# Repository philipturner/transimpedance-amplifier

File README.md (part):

# Transimpedance Amplifier

<p align="center">
&nbsp;
  
&nbsp;&nbsp;
  
&nbsp;&nbsp;
  
&nbsp;
</p>

Phase 0.1 of the [APM Roadmap](https://github.com/philipturner/apm-roadmap)

Objective: Gather as much data as possible about the TIA sensor of an STM, using both theory and experiment.

Deadline: September 30, 2025 for the first physical prototype

Completed: November 7, 2025

Table of Contents:
- [July 26, 2025](#july-26-2025)
- [July 27, 2025](#july-27-2025)
- [July 28, 2025](#july-28-2025)
- [July 29, 2025](#july-29-2025)
- [August 3, 2025](#august-3-2025)
- [August 4, 2025](#august-4-2025)
- [August 5, 2025](#august-5-2025)
- [August 6, 2025](#august-6-2025)
- [August 7, 2025](#august-7-2025)
- [August 8, 2025](#august-8-2025)
- [August 9, 2025](#august-9-2025)
- [August 16, 2025](#august-16-2025)
- [August 18, 2025](#august-18-2025)
- [August 20, 2025](#august-20-2025)
- [August 22, 2025](#august-22-2025)
- [August 23, 2025](#august-23-2025)
- [August 26, 2025](#august-26-2025)
- [August 27, 2025](#august-27-2025)
- [August 28, 2025](#august-28-2025)
- [August 29, 2025](#august-29-2025)
- [September 1, 2025](#september-1-2025)
- [September 7, 2025](#september-7-2025)
- [September 8, 2025](#september-8-2025)
- [September 9, 2025](#september-9-2025)
- [September 10, 2025](#september-10-2025)
- [September 11, 2025](#september-11-2025)
- [September 12, 2025](#september-12-2025)
- [September 15, 2025](#september-15-2025)
- [September 16, 2025](#september-16-2025)
- [September 17, 2025](#september-17-2025)
- [September 18, 2025](#september-18-2025)
- [September 19, 2025](#september-19-2025)
- [September 20, 2025](#september-20-2025)
- [September 21, 2025](#september-21-2025)
- [September 22, 2025](#september-22-2025)
- [September 23, 2025](#september-23-2025)
- [September 24, 2025](#september-24-2025)
- [September 25, 2025](#september-25-2025)
- [October 22, 2025](#october-22-2025)
- [October 23, 2025](#october-23-2025)
- [October 24, 2025](#october-24-2025)
- [October 26, 2025](#october-26-2025)
- [October 29, 2025](#october-29-2025)
- [October 30, 2025](#october-30-2025)
- [October 31, 2025](#october-31-2025)
- [November 2, 2025](#november-2-2025)
- [November 3, 2025](#november-3-2025)
- [November 5, 2025](#november-5-2025)
- [November 6, 2025](#november-6-2025)
- [November 7, 2025](#november-7-2025)

## July 26, 2025

Three simulation tasks, in chronological order
1) Understand/simulate why coarse tip approach takes so long
    - Understand specific algorithms for moving the coarse motor (approach & retract) without frictional backlash causing a tip crash
    - Understand maximum speeds of piezo motors
2) Simulate imperfect DAC-driven cancellation with a fixed value compensation capacitor
    - Use the tip-sample capacitance of a plausible geometry, derived with FEA
    - Include a finite insulation resistance
3) Fully understand the art of cabling analog lines in/out of UHV chambers + instrumentation amplifiers + ground loops
    - Include EMI and digital coupling from the bias DAC + ADC + SPI ports + power supply system

Notes about simulations:
- Make compromises to reduce the number of variables in each simulation, making it practical to set up
    - The simulations are not particularly computationally intensive, often 1-variable analytical functions, Fourier transforms, and integrals of power spectral density.
    - Likely using a combination of Google Sheets and single-file scripts hosted on GitHub Gist, hyperlinked to this repo.
- Exploit recently acquired skills in finite element analysis and the theory of EMI/grounding/shielding
- <b>Early IRL hardware tests may fail some requirements for system performance</b>, which are assumed or optimized for in the simulations

---

Simultaneously performing a low-cost physical test with a badly shielded IRL model
- Gather as much data, as early as possible
- Pipeline the phases of design elaboration
- Later stages include electromagnetic shielding, interfaces with automated electronics for the I/O voltages, then the logical transition to Phase 0.2

Primary blockers to first physical prototype:
- Lack of understanding about electrical performance of reversible DUT connection point (DUT = resistor, capacitor)
- Need to elaborate on requirements for ventilation from acid fumes, and other specific equipment to order for hand soldering
- Need to resolve the issues with incorrect/unnecessary bypass/decoupling capacitors
  - It is a very bad idea to omit all the capacitors, without at least giving it some rigorous consideration
- Need to resolve the missing/incorrect KiCad symbols and footprints for each IC. Organize the footprints on a physical PCB model and become familiar with the specific pin functions & positions.
- Need to clarify the bothersome trace width variable

<b>Fast-track work on the physical prototype.</b> Ensure that all fabrication equipment, testing equipment, and circuit parts are delivered by August 12, 2025. In any leftover time until August 12, I can return to the three simulation tasks.

An appropriate name for this is ["STM Experiment #3"](https://www.youtube.com/watch?v=IUPDecnuzO4). The experiments may not logically build on each other. For example, a single 1000 V linear amplifier doesn't logically follow a capacitive displacement sensor. However, it can still be catalogued as `n + 1` to show the iterative nature of design elaboration & exploration.

## July 27, 2025

One of the most important tests should be feedback loop stability. With the SPICE simulations, I can predict what values for input capacitance will send the circuit into oscillations. Pick a conservative value(s) for a capacitor DUT that satisfies this condition, without making the current exceed its dynamic range (simply reduce the frequency of the signal).

The first prototype will test two TIA variants. The first will be the standard OPA627 + 100 MΩ design used in most DIY STM projects. This will give a baseline for tracing failures, if the complex 2-stage design does not work at all.

I should see whether testing equipment, such as a handheld oscilloscope, can generate an input function. This would remove the need for a hard-coded triangle wave generator on the PCB. However, I might include the triangle wave generator anyway, for completeness and/or more debugging options. It also provides experience designing with digital/nonlinear components (comparator & Schmitt trigger), which may couple into the analog components against my wishes. There should be a simple way to disconnect the generator from power pins. It could be helpful to make the generator's capacitor swappable, so the frequency can change.

## July 28, 2025

I am starting to read large swaths of the IPC 7351 standard, February 2005 revision. This project will resolve my frustration with non-standardization of resistor & capacitor footprints. It substantiates a growing realization across many engineering projects, that complex systems have many variables. They demand significant amounts of data to wrap my head around. I am not satisfied with arbitrary guesses and binary yes/no "it worked" tests, with no explanation of how this choice contributed to a reduction in UHV chamber cost.

> My objective is obtain better control over the usability, performance, and cost of my end product(s).

I feel more comfortable creating my own footprints from scratch, where I can trust every parameter used to derive every dimension. I will compare my footprints to those from vendors, SnapEDA, and KiCad libraries.

## July 29, 2025

A few more things I want to do, before the 1st prototype:
- Run a SPICE simulation of the stability of a feedback loop with OPA627 + 100 MΩ. Check the limits of stability with the parasitic capacitance of the resistor.
  - Include a model of OPA637 to understand why that's not okay.
  - If OPA637 passes in the simulations, the test board will include a third TIA, OPA637 + 100 MΩ + no parallel capacitor.
    - Even if it doesn't pass, include the actual combination IRL, to prove that it oscillates when tested!
    - Unless this could plausibly impair the operation of the other amplifiers, and there's no way to switch off power to the OPA637.
    - Will severe oscillation conditions cause damage to the component and/or its power supply?
- Get more rigorous calculations of the parasitics for the components, and of the potentiometers.
- Design custom footprints for the capacitors and trimpots as well, in the first step. I previously planned to just wrap my head around the ICs + large resistors first. Instead, I should get the entire system specified at the highest (symbolic) level, and elaborate on the physical layout once that's fixed.
  - Bypass/decoupling capacitors are intentionally omitted at this stage.
  - The exact resistor values for the AD8615 voltage divider are omitted at this stage. Also not worrying about whether the two polarities of the divider cross through the GND net.
- Calculate the expected noise (e.g. Johnson noise from resistors in 2nd stage), bandwidth of the oscilloscope ADC, and consider electromagnetic shielding.
  - Consider an artificial bandwidth limiter with a transfer function similar to the ADS8699. This probably requires another IC. Good practice in selecting arbitrary op-amps for real world situations of need.
  - Calculate the leakage current at the physical current input junction + corresponding reversible DUT port. Compare the leakage current to the noise floor.
- Prepare a list of through-hole DUT components. Elaborate on whether it's a single DUT port for all 2&ndash;3 amplifiers, or a separate port for each.

I just learned/remembered that OPA627 and OPA637 are very old and expensive (\~$30). I'll have to revise these plans, to use newer and cheaper chips like OPA828 (\~$7). Or scrap the entire concept of additional 1-stage amplifiers to save time, depending on motivation.

## August 3, 2025

This project is on track to blow far north of its time budget. I'll have to compromise.

Permitted:
- Delete the oscilloscope from the workflow (yay!)
- Read [MT-015](https://www.analog.com/media/en/training-seminars/tutorials/MT-015.pdf), [MT-017](https://www.analog.com/media/en/training-seminars/tutorials/MT-017.pdf), [MT-019](https://www.analog.com/media/en/training-seminars/tutorials/MT-019.pdf), [MT-021](https://www.analog.com/media/en/training-seminars/tutorials/MT-021.pdf), [MT-090](https://www.analog.com/media/en/training-seminars/tutorials/MT-090.pdf) to understand the chips I'm working with
- Make an entirely custom footprint for every electronic part

Disallowed:
- Run a simulation to understand whether quantization noise and time jitter makes capacitance compensation unviable, with my novel approach
- Use any chips that require reflow soldering
- The analog triangle wave generator from the fast low-noise TIA paper. We're already synthesizing arbitrary waveforms with the DAC, with adjustable frequencies.

The near-term deliverable will pair the Teensy with a single DAC channel (DAC81401) and a single ADC channel (ADS8699), with a nerfed system bandwidth of 15 kHz. I really wanted a higher frequency to debug the first step. Unfortunately, the 500 kHz chip, ADS86861W, requires reflow soldering. I'll defer contemplating the ramifications of this omission to a later date.

---

Comments on the previous journal entry:
- Johnson noise is comparable to e<sub>n</sub>C noise, at 15 kHz bandwidth + 2nd order rolloff.
  - 6σ noise from capacitance is <b>5.2 pA</b>, provided just the 9.2 pF input capacitance of the AD8615 (conservative estimate, summing the differential and common-mode capacitance)
  - 6σ noise from capacitance is <b>24.7 pA</b>, when moved outside the UHV chamber, adding 35 pF to the capacitance to model a coaxial cable
  - 6σ Johnson noise from a 100 MΩ resistor is <b>10.9 pA</b>
  - 6σ Johnson noise from a 300 MΩ resistor is <b>6.3 pA</b>
  - 6σ Johnson noise from a 1 GΩ resistor is <b>3.5 pA</b>
- The noise signal appears as ~1 mV at the ADC.
  - 1-stage with OPA828ID:
    - 15.0 pF
    - 100 MΩ
    - 6σ noise envelope is <b>1.2 mV</b>
  - 2-stage with AD8615:
    - 9.2 pF
    - 300 MΩ
    - 6σ noise envelope is <b>2.4 mV</b>
- Don't need to construct an artificial 15 kHz filter out of discrete components. I'm using the actual ADS8699 chip in the circuit board now.
- 15 kHz bandwidth is more than enough for the STM feedback loop. If anything, I would use digital filtering to reduce it to the single kHz range, reducing the 6σ current noise to ~1 pA.

Source: [Transimpedance Amplifier (Google Sheets)](https://docs.google.com/spreadsheets/d/1QVJOiaRJbdRXN7CXii3z91K5A64h3VmgLCsRjpDpIrQ/edit?usp=sharing)

## August 4, 2025

<p align="center">
&nbsp;
  
&nbsp;&nbsp;
  
&nbsp;
</p>

## August 5, 2025

It is becoming very clear that I want to run this simulation about capacitive displacement sensing.

The simulation will have an analytical (frequency domain) and numerical (time domain) part.
- Analytical stuff:
  - Theoretical model of the distribution of quantization noise among the DACs (evenly across the Nyquist bandwidth)
    - Ensure the sine wave frequency is indivisible by the quantization frequency (100 kSPS)
    - Concerned about the variable-voltage approach not being able to perfectly cancel the quantization noise
  - Model of the integrated e<sub>n</sub>C noise after lock-in amplification
  - Model of the transfer function for the 2-stage TIA, which might change with input capacitance (?)
- Numerical stuff:
  - FP64 for the simulations to avoid concerns about rounding error, over long time intervals for lock-in amplification
    - Time stepping resolution 1&ndash;2 orders of magnitude better than the 100 kSPS sampling rate
  - Exact algorithm for a digital filter approximating a first-order or second-order lowpass
    - Validate that the filters have the expected gain falloff, by running a sweep over sine wave frequencies
    - The filter is affected by the time step size
  - Simulate the two DACs being out of sync, which probably cannot be represented in an analytical frequency domain model
- A way to include the effects of shot noise from background capacitance into the results of the numerical part

Imperfections covered in the simulation:
- Inaccurate matching of a fixed-value capacitor to the tip-sample capacitance (up to a factor of 10 in either direction)
- Overloading the maximum TIA voltage due to the transfer function exceeding the ADC @ 15 kHz. Specifically, overloading from signals in the 15&ndash;30 kHz range.
- Quantization of the two DAC signals causing a strange division of the Gaussian quantization errors (?)
- The two DACs being out of sync (not yet figured out the exact amount of delay to test)

Imperfections not covered:
- Time jitter in the ADC and/or DACs
- Switching transients in the DACs
- Interference from acoustic noise
- Interference from a finite insulation resistance in the compensation capacitor

First step:
- Attempt to find a formula for the RMS current of two cancelling signals, slightly phase shifted
- Address the low-hanging fruit, of a frequency domain analysis of the effect of quantization noise

Second step:
- Refresh myself on the analytical formulas for transfer function of the fast low-noise TIA, stability conditions, and location of the 2nd pole
- Figure out the exact potentiometer values appropriate for this circuit
- For simplicity (to save time), the simulation will assume the potentiometers are perfectly matched, to an infinite resolution

Since I am in the car right now, I cannot work on the first step. Therefore, I will proceed with specifying the near-term experiment with reduced scope.

---

Interesting observations:
- ADS8681W is not even in stock, although Mouser expects a new batch in late August
- Only Mouser has stock of DAC81402, DigiKey does not
- Amazon Basics 6LR61 is probably sufficient for the 9V batteries

## August 6, 2025

I understand how the AH2550 / AH2700 works now. Used this knowledge to understand possible limitations in my custom metrology setup.

[Capacitive Displacement Sensing (Google Sheets)](https://docs.google.com/spreadsheets/d/1fhiZoWPt_2P-jLdGjmx1e9VDYEp9JpBjLP0ZZkT_46Y/edit?usp=sharing)

Done with the investigation of capacitive displacement sensing. Modulation voltage is 10 V, carrier frequency is 10 kHz. Pushing the limits of the DAC and ADC. Digitization rate in the DAC assumed 50 kSPS to give a conservative estimate for quantization noise.

Assuming the two capacitances can be compensated to 99.9% accuracy, static magnitude and shot noise of the background signal are not limiting factors. The ratio of 1 LSB in the ADC to the static background signal (~565 pA) is 1:1800.

Dominant issue is dynamic quantization noise. In the AH2550/AH2700, the quantization errors from the two stimulus signals (near-)perfectly cancel. In my design, they do not.

## August 7, 2025

I did some work on the voltage limiter for the 2nd stage of the 2-part TIA. I went with copying the part models from the latest iteration of the design by Schmid et al. There is an extremely large space of manufacturers and part variants, for diodes and BJTs that are almost the same.

I was about to inspect more details of these parts, and the conditions they're subjected to, to understand more about what's going on. Instead, I deferred that task to a later date. Just as elaboration on the specific decoupling network for each IC, is out of scope for today. Except for the fact that AD8615's decoupling network uses a 1 kΩ potentiometer and a 3.3V Zener.

Thanks to Michael Schmid for filling me in on the recommended decoupling network, thus saving a lot of time. Chips like the ADC and DAC, or other parts where decoupling is critical to operation, typically have a manufacturer's suggested configuration on the datasheet.

[Discrete Semiconductors (Google Sheets)](https://docs.google.com/spreadsheets/d/1FA-BcQ8bDqJqKHbvW08lza3Lz3hW-CrOkspl6eD3IWo/edit?usp=sharing)

I am returning to the KiCad project, currently in the stage of specifying the symbolic schematic. I've specifically declared PCB geometry and footprints out of scope. When downloading part symbols from vendor websites, I neglect the footprints and 3D models. However, I'm aware of the specific package. For example, I chose the THT package over the SMT package for the voltage regulators. Although the part becomes larger, the pin count reduces from 8 to 3; the pin mapping is more direct. Everywhere else, I prefer an SMT package if possible.

I will rename the hierarchical sheets for the transimpedance amplifiers, avoiding words that start with a number. I will also attempt to create a deeper level of hierarchy for the 2 stages of the 2-part TIA. Then, I will copy as many part symbols as possible, for everything except small resistors, small capacitors, and reversible connection ports.

Tomorrow, I should be able to start specifying in/out lines for each module. For example, distributing regulated voltages from the power module to each client module. The low-frequency decoupling capacitor and voltage divider for the AD8615's ±5 V lines will probably be encapsulated within the sub-sheet of the 2-stage TIA. All other regulators have their networks specified in the power module.

> A deep investigation is warranted for the subtle detail of a 0.01 μF C2 on the LM78L datasheet / 0.1 μF on LM79L. Approaching the severity of declaring all footprints for every circuit part "custom" to achieve control of the little details. Again, beyond the scope of the tasks outlined above.

## August 8, 2025

Today, my objective was to understand more about the parasitic capacitance of the TIA feedback resistor.

_Cross-section view of the Elmer simulation results, showing where the electrostatic energy is concentrated. The sharp ends of the conductors contain 90% of the energy associated with capacitance._

I created a multi-material model of the Vishay 0805 <b>thick film</b> chip resistor. Each conductor is 10	μm thick and wraps around from top to bottom. The bulk of the component is a slab of alumina, parameterized with ε<sub>r</sub> = 9.1. The resistive element was replaced with air. After several hours of troubleshooting, I got the simulation to work. The initial result, ~40 fF, was unexpectedly small. I tried refining the mesh, to see whether the result would change.

| Node Count | Element Order | Mutual Capacitance (C<sub>12</sub>) |
| ---------: | ------------: | ----------------------------------: |
| ~5,000     | 1             | 39.61 fF                            |
| ~14,000    | 1             | 37.83 fF                            |
| ~40,000    | 1             | 36.93 fF                            |
| ~150,000   | 1             | 36.46 fF                            |

In his [ultra-low noise qPlus AFM sensor design](https://doi.org/10.1063/1.4993737), Geissibl used an 0805 <b>thick film</b> chip resistor ([datasheet](https://www.te.com/usa-en/product-1625862-1.datasheet.pdf)). He reported 150 fF, which agrees with the generally\* assumed 100 fF for transimpedance amplifiers. I simulated an almost identical geometry, and was off by a factor of 4.

> \*Art of Electronics, fast low-noise TIA paper

Vishay [measured the parasitics](https://www.vishay.com/docs/60107/freqresp.pdf) of <b>thin film</b> chip resistors, going as large as 0603. The capacitances follow a predictable scaling law. I'll develop a model that accepts any resistor geometry, and matches them to the Vishay data.

| Source           | Case Size | L    | W    | H    | T2   |
| ---------------- | --------- | ---: | ---: | ---: | ---: |
| Vishay (2009)    | 0201      | 0.51 | 0.25 | n/a  | 0.20 |
| Vishay (2009)    | 0402      | 1.02 | 0.51 | n/a  | 0.29 |
| Vishay (2009)    | 0603      | 1.63 | 0.81 | n/a  | 0.49 |
| Vishay D/CRCW e3 | 0402      | 1.00 | 0.50 | 0.35 | 0.20 |
| Vishay D/CRCW e3 | 0603      | 1.55 | 0.85 | 0.45 | 0.30 |
| Vishay D/CRCW e3 | 0805      | 2.00 | 1.25 | 0.50 | 0.30 |
| TE               | 0805      | 2.00 | 1.20 | 0.40 | 0.30 |

_Part dimensions from three literature sources. All dimensions are in millimeters._

Use thick film 0603 as an "origin" or normalized value, from which other capacitances are scaled. It is the case size I will use in the PCB. Scaling behavior comes mostly from lengthening and separating the sharp ends of the conductors. Scaling of height could both increase and decrease capacitance, making it troublesome to model. Therefore, we don't need to worry about the lack of height data for Vishay (2009).

I developed two fittings of the data ([source](https://docs.google.com/spreadsheets/d/1QVJOiaRJbdRXN7CXii3z91K5A64h3VmgLCsRjpDpIrQ/edit?usp=sharing)). One extrapolates based on the parallel plate model. The other extrapolates based on the parallel wire model. Here are the final values for capacitance, after correcting for the discrepancy between "flip chip" and "wrap around".

| Source           | Case Size | parallel plate | parallel wire |
| ---------------- | --------- | ---: | ---: |
| Vishay (2009)    | 0201      | 33.9	fF | 28.2	fF |
| Vishay (2009)    | 0402      | 35.3	fF | 41.0 fF |
| Vishay (2009)    | 0603      | 60.3	fF | 60.3 fF |
| Vishay D/CRCW e3 | 0402      | 24.9	fF | 37.8 fF |
| Vishay D/CRCW e3 | 0603      | 45.4	fF | 59.0 fF |
| Vishay D/CRCW e3 | 0805      | 66.7	fF | 81.1 fF |
| TE               | 0805      | 61.4	fF | 77.9 fF |

The Vishay data predicts ~74 fF, double the simulation result.

<b>Option 1:</b> Continue trying things in the simulator, to raise the lower bound for capacitance with an 0603 case size. This single parasitic value is the reason for the entire 2nd stage of the TIA. If the cutoff frequency is ~13 kHz, the ADS8699 cannot facilitate tuning.

<b>Option 2:</b> Switch to the larger 0805 size, which will certainly have more capacitance than 0603 and match previous expectations.

Conclusion: Go with option 2, reworking the equations to handle an unknown value in the range of 74&ndash;250 fF. If this makes the design unworkable, revert to option 1. Accept reduced tunability at a tradeoff of faster time to completion. If the range of 74&ndash;150 fF is more tunable than 150&ndash;250 fF, this is very good.

> Realization: Simulation work will only raise the lower bound to capacitance. Marginal improvements to the lower bound will cost disproportionately more effort. There is no upper bound. Poor PCB design will add parasitic coupling to the lower bound.
>
> C<sub>f</sub> &ge; 74 fF
>
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
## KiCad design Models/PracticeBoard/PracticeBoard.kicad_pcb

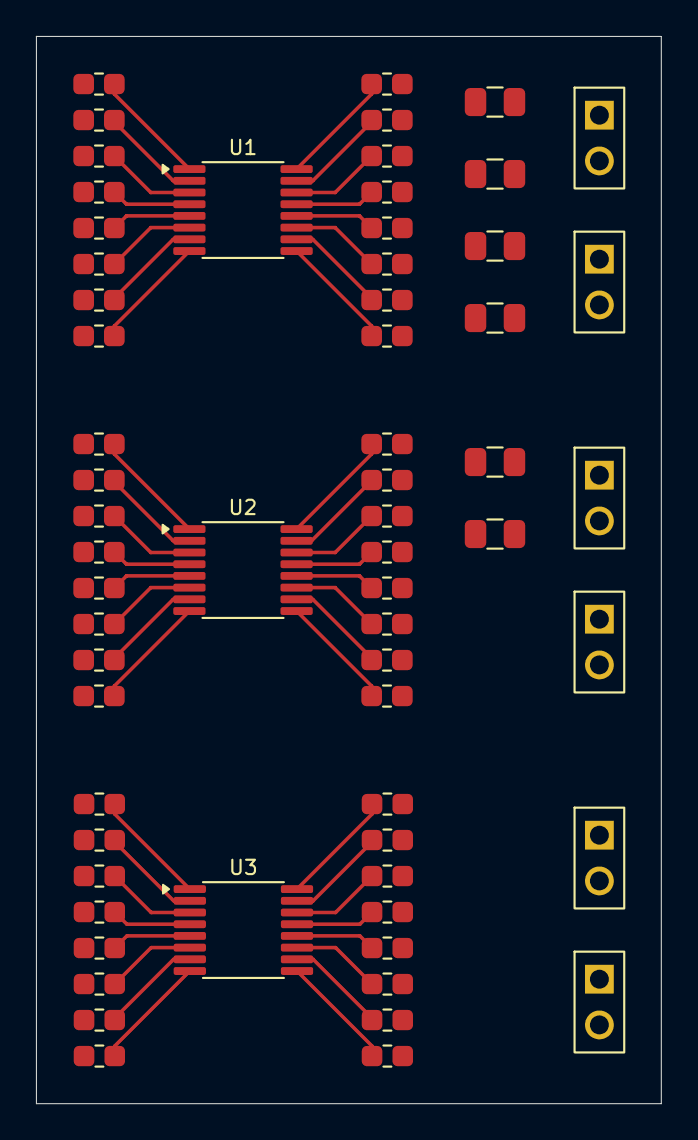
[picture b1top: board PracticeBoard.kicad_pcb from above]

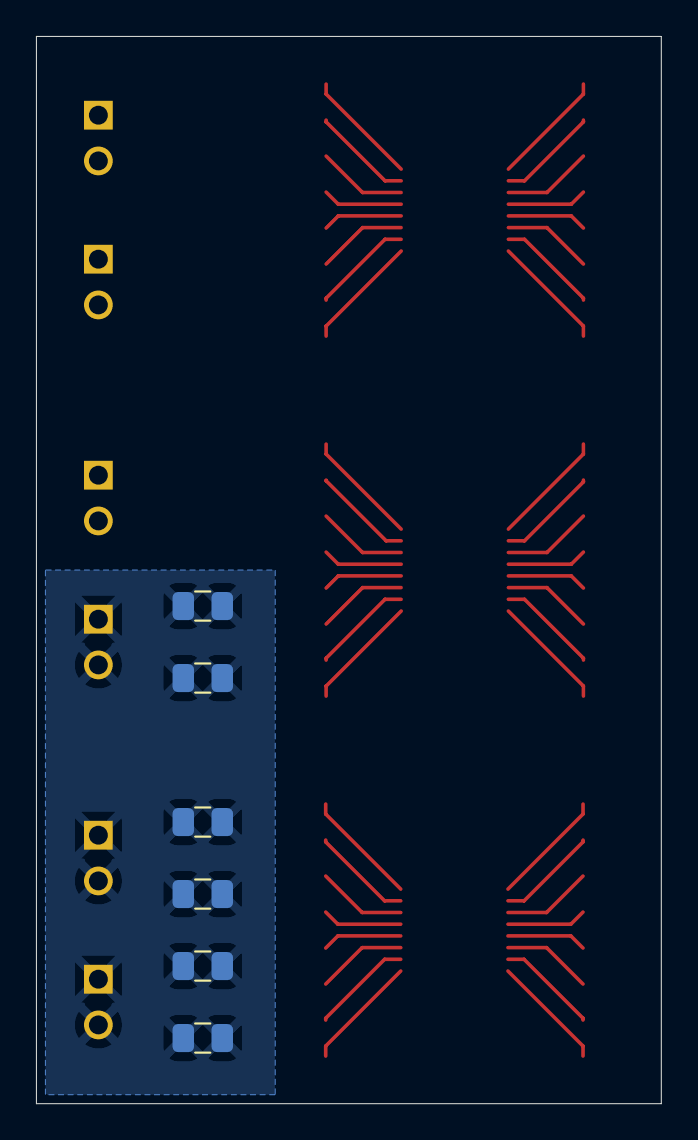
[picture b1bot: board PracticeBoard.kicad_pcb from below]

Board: 2 copper layers, 34.7 x 59.3 mm, 69 parts (6 on the bottom side), 49 nets.

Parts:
J1, J2, J3, J4, J5, J6: Conn_01x02_Pin; PinHeader_1x2
R1, R2, R3, R4, R5, R6, R7, R8, R9, R10, R11, R12: 10k, 0805; RESC0805
R13, R14, R15, R16, R17, R18, R19, R20, R21, R22, R23, R24, R25, R26, R27, R28, R29, R30, R31, R32, R33, R34, R35, R36, R37, R38, R39, R40, R41, R42, R43, R44, R45, R46, R47, R48, R49, R50, R51, R52, R53, R54, R55, R56, R57, R58, R59, R60: 10k, 0603; RESC0603
U1, U2, U3: XMC1100; ADS8699

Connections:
GND: J4.1, J4.2, J5.1, J5.2, J6.1, J6.2, R7.1, R7.2, R8.1, R8.2, R9.1, R9.2, R10.1, R10.2, R11.1, R11.2, R12.1, R12.2
unnamed: R22.1, U1.9 (*RST)
unnamed: R15.2, U1.3 (AGND)
unnamed: R20.2, U1.8 (AIN_GND)
unnamed: R18.2, U1.7 (AIN_P)
unnamed: R25.1, U1.14 (ALARM/SDO-1/GPO)
unnamed: R17.2, U1.2 (AVDD)
unnamed: R26.1, U1.11 (CONVST/*CS)
unnamed: R19.2, U1.1 (DGND)
unnamed: R21.1, U1.16 (DVDD)
unnamed: R16.2, U1.6 (REFCAP)
unnamed: R14.2, U1.5 (REFGND)
unnamed: R13.2, U1.4 (REFIO)
unnamed: R23.1, U1.15 (RVS)
unnamed: R28.1, U1.12 (SCLK)
unnamed: R24.1, U1.10 (SDI)
unnamed: R27.1, U1.13 (SDO-0)
unnamed: R38.1, U2.9 (*RST)
unnamed: R31.2, U2.3 (AGND)
unnamed: R36.2, U2.8 (AIN_GND)
unnamed: R34.2, U2.7 (AIN_P)
unnamed: R41.1, U2.14 (ALARM/SDO-1/GPO)
unnamed: R33.2, U2.2 (AVDD)
unnamed: R42.1, U2.11 (CONVST/*CS)
unnamed: R35.2, U2.1 (DGND)
unnamed: R37.1, U2.16 (DVDD)
unnamed: R32.2, U2.6 (REFCAP)
unnamed: R30.2, U2.5 (REFGND)
unnamed: R29.2, U2.4 (REFIO)
unnamed: R39.1, U2.15 (RVS)
unnamed: R44.1, U2.12 (SCLK)
unnamed: R40.1, U2.10 (SDI)
unnamed: R43.1, U2.13 (SDO-0)
unnamed: R54.1, U3.9 (*RST)
unnamed: R47.2, U3.3 (AGND)
unnamed: R52.2, U3.8 (AIN_GND)
unnamed: R50.2, U3.7 (AIN_P)
unnamed: R57.1, U3.14 (ALARM/SDO-1/GPO)
unnamed: R49.2, U3.2 (AVDD)
unnamed: R58.1, U3.11 (CONVST/*CS)
unnamed: R51.2, U3.1 (DGND)
unnamed: R53.1, U3.16 (DVDD)
unnamed: R48.2, U3.6 (REFCAP)
unnamed: R46.2, U3.5 (REFGND)
unnamed: R45.2, U3.4 (REFIO)
unnamed: R55.1, U3.15 (RVS)
unnamed: R60.1, U3.12 (SCLK)
unnamed: R56.1, U3.10 (SDI)
unnamed: R59.1, U3.13 (SDO-0)

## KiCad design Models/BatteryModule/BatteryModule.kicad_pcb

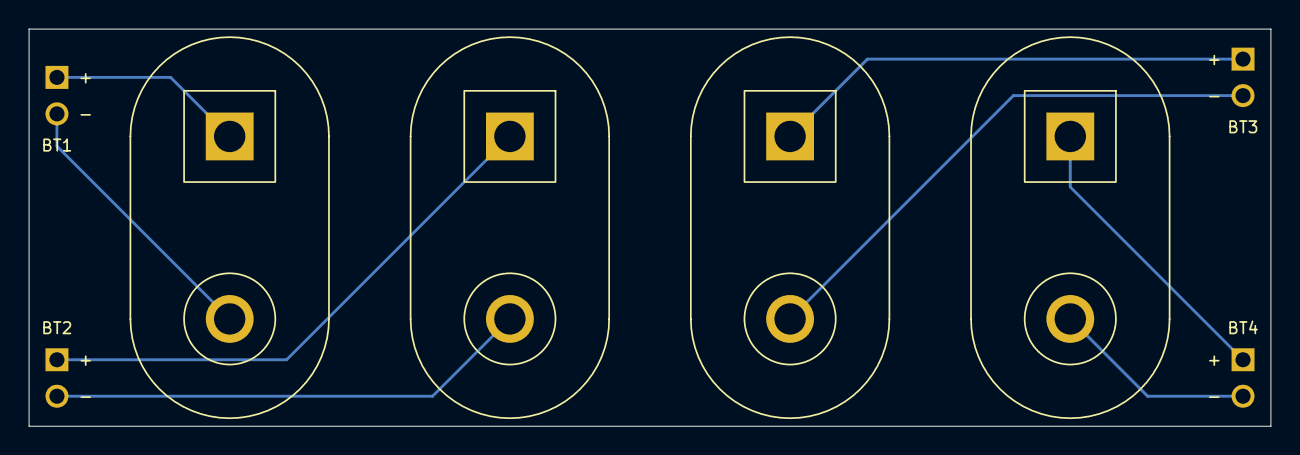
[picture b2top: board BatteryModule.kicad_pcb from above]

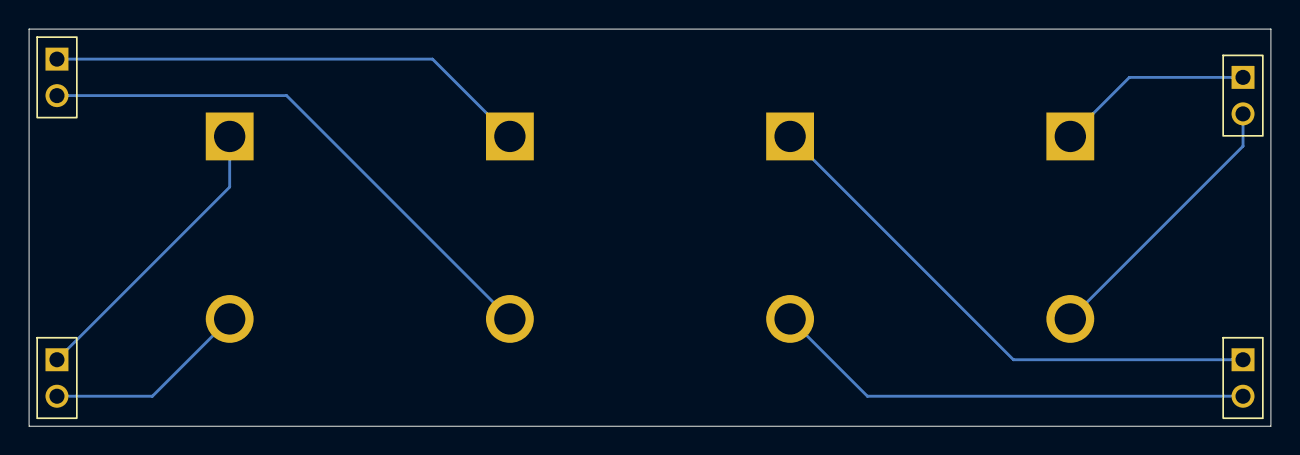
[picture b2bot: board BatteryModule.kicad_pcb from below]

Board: 2 copper layers, 86.4 x 27.6 mm, 8 parts (4 on the bottom side), 8 nets.

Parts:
J1, J2, J7, J8: Conn_01x02_Pin; PinHeader_1x2
J3, J4, J5, J6: Keystone_968

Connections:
unnamed: J1.1, J3.1 (+)
unnamed: J1.2, J3.2 (-)
unnamed: J2.1, J4.1 (+)
unnamed: J2.2, J4.2 (-)
unnamed: J5.1 (+), J7.1
unnamed: J5.2 (-), J7.2
unnamed: J6.1 (+), J8.1
unnamed: J6.2 (-), J8.2

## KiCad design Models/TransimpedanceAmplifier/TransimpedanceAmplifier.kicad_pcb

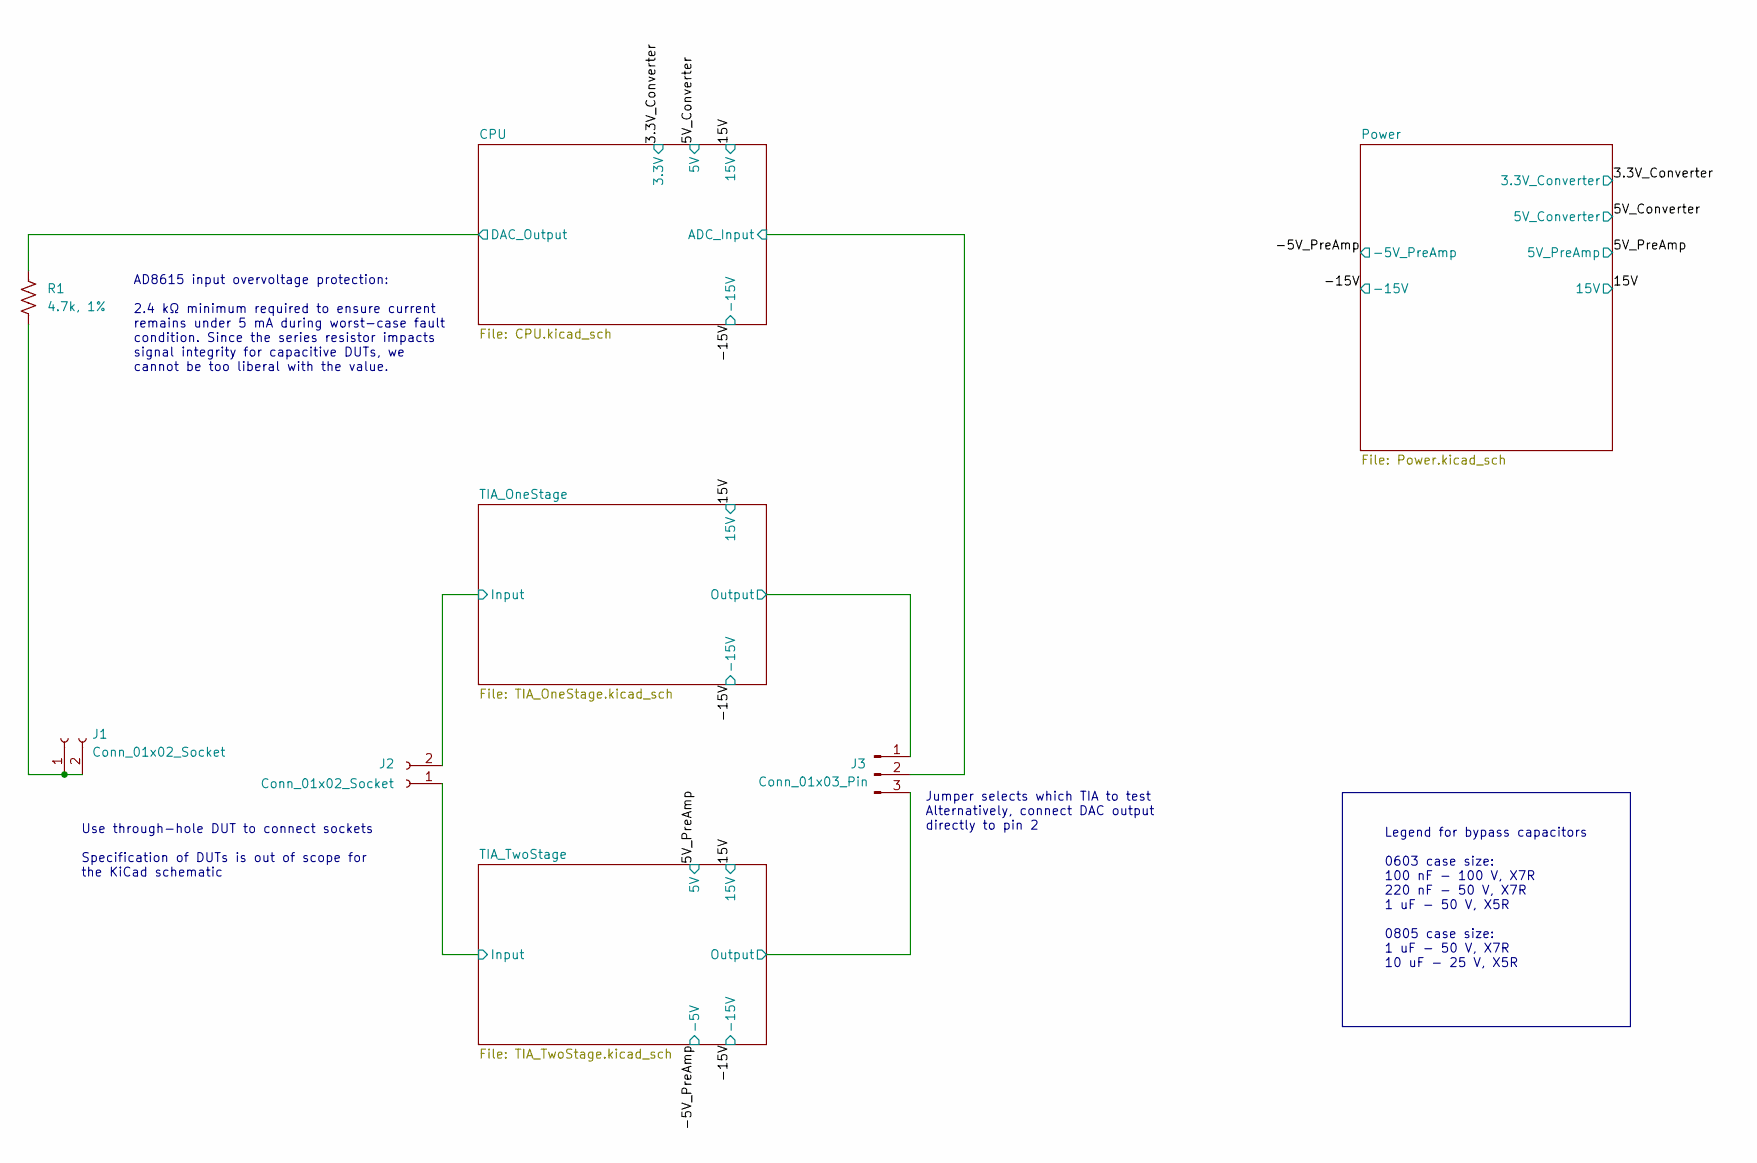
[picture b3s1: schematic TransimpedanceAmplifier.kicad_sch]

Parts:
J1, J2: Conn_01x02_Socket; PinSocket_1x2
J3: Conn_01x03_Pin; PinHeader_1x3
R1: 4.7k, 1%; RESC0603

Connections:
/CPU/ADC_Input: J3.2; also elsewhere on the board
/CPU/DAC_Output: R1.1; also elsewhere on the board
/TIA_OneStage/Input: J2.2; also elsewhere on the board
/TIA_OneStage/Output: J3.1; also elsewhere on the board
/TIA_TwoStage/Input: J2.1; also elsewhere on the board
/TIA_TwoStage/Output: J3.3; also elsewhere on the board
unnamed: J1.1, J1.2, R1.2

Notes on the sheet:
Legend for bypass capacitors 0603 case size: 100 nF - 100 V, X7R 220 nF - 50 V, X7R 1 uF - 50 V, X5R 0805 case size: 1 uF - 50 V, X7R 10 uF - 25 V, X5R
AD8615 input overvoltage protection: 2.4 kΩ minimum required to ensure current remains under 5 mA during worst-case fault condition. Since the series resistor impacts signal integrity for capacitive DUTs, we cannot be too liberal with the value.
Jumper selects which TIA to test Alternatively, connect DAC output directly to pin 2
Use through-hole DUT to connect sockets Specification of DUTs is out of scope for the KiCad schematic

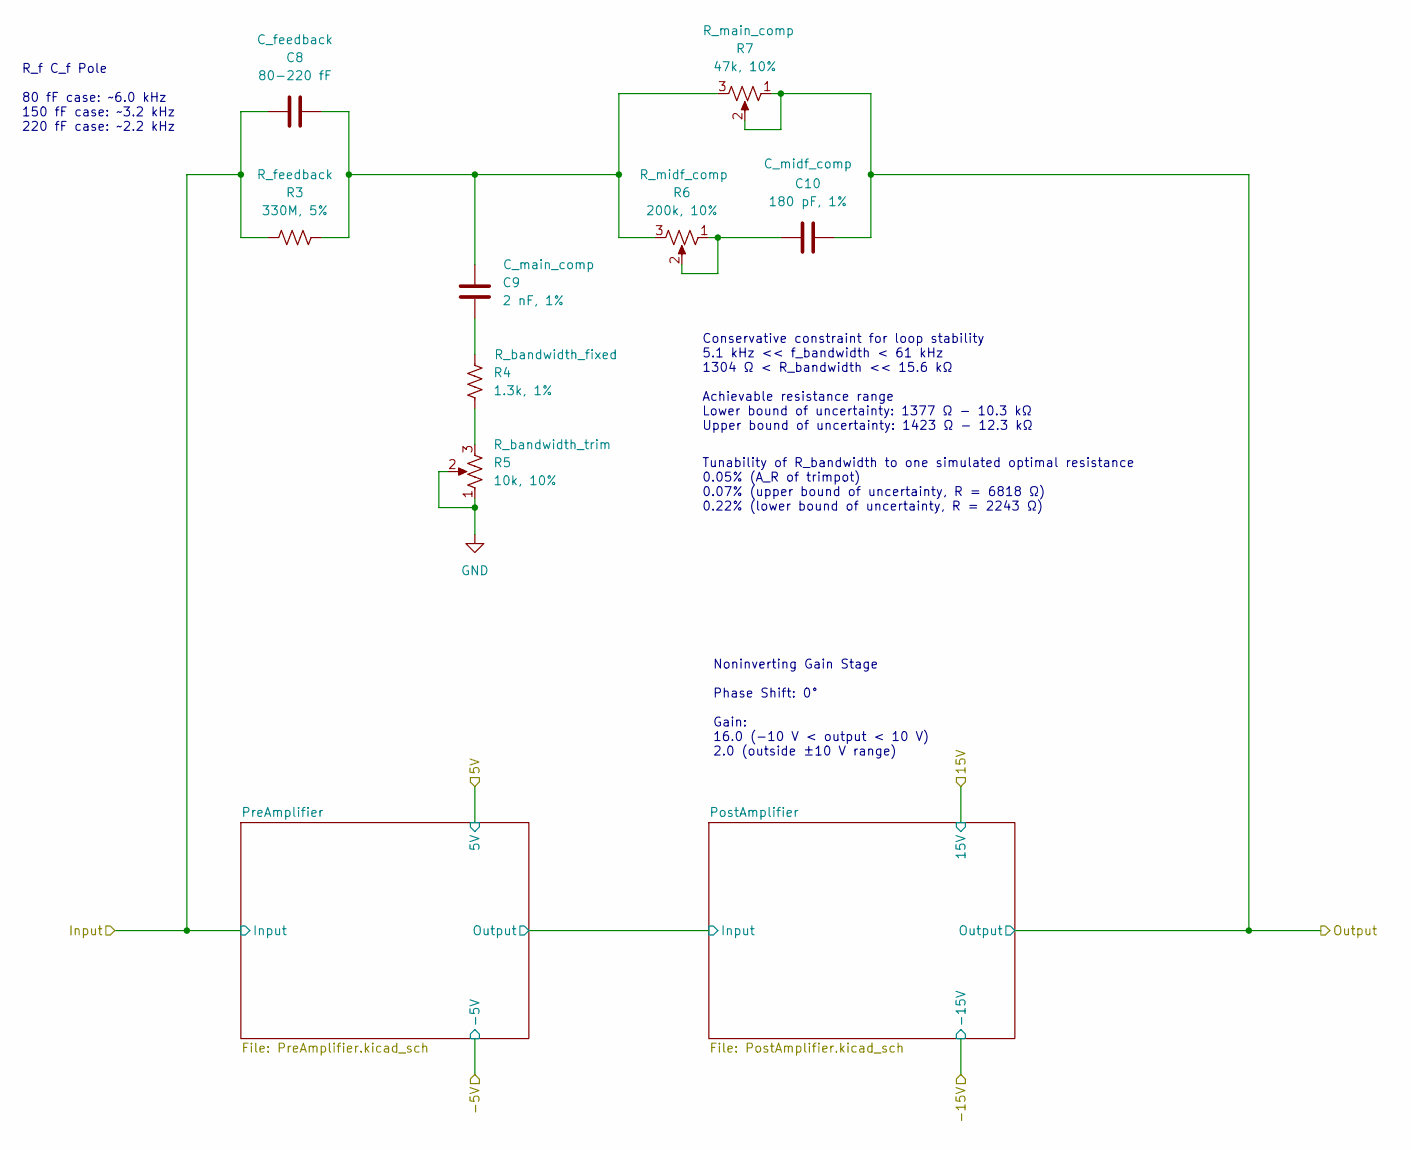
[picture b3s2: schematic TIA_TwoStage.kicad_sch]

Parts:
C8: 80-220 fF
C9: 2 nF, 1%; CAPC0603
C10: 180 pF, 1%; CAPC0603
R3: 330M, 5%; RESC0805
R4: 1.3k, 1%; RESC0603
R5: 10k, 10%; Bourns_3296Y
R6: 200k, 10%; Bourns_3296Y
R7: 47k, 10%; Bourns_3296Y

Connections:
/TIA_TwoStage/Input: C8.1, R3.1; also elsewhere on the board
/TIA_TwoStage/Output: C10.2, R7.1, R7.2; also elsewhere on the board
GND: R5.1, R5.2; also elsewhere on the board
unnamed: C8.2, C9.1, R3.2, R6.3, R7.3
unnamed: C9.2, R4.1
unnamed: C10.1, R6.1, R6.2
unnamed: R4.2, R5.3

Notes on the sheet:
Conservative constraint for loop stability 5.1 kHz << f_bandwidth < 61 kHz 1304 Ω < R_bandwidth << 15.6 kΩ Achievable resistance range Lower bound of uncertainty: 1377 Ω - 10.3 kΩ Upper bound of uncertainty: 1423 Ω - 12.3 kΩ
Noninverting Gain Stage Phase Shift: 0° Gain: 16.0 (-10 V < output < 10 V) 2.0 (outside ±10 V range)
Tunability of R_bandwidth to one simulated optimal resistance 0.05% (A_R of trimpot) 0.07% (upper bound of uncertainty, R = 6818 Ω) 0.22% (lower bound of uncertainty, R = 2243 Ω)
R_f C_f Pole 80 fF case: ~6.0 kHz 150 fF case: ~3.2 kHz 220 fF case: ~2.2 kHz

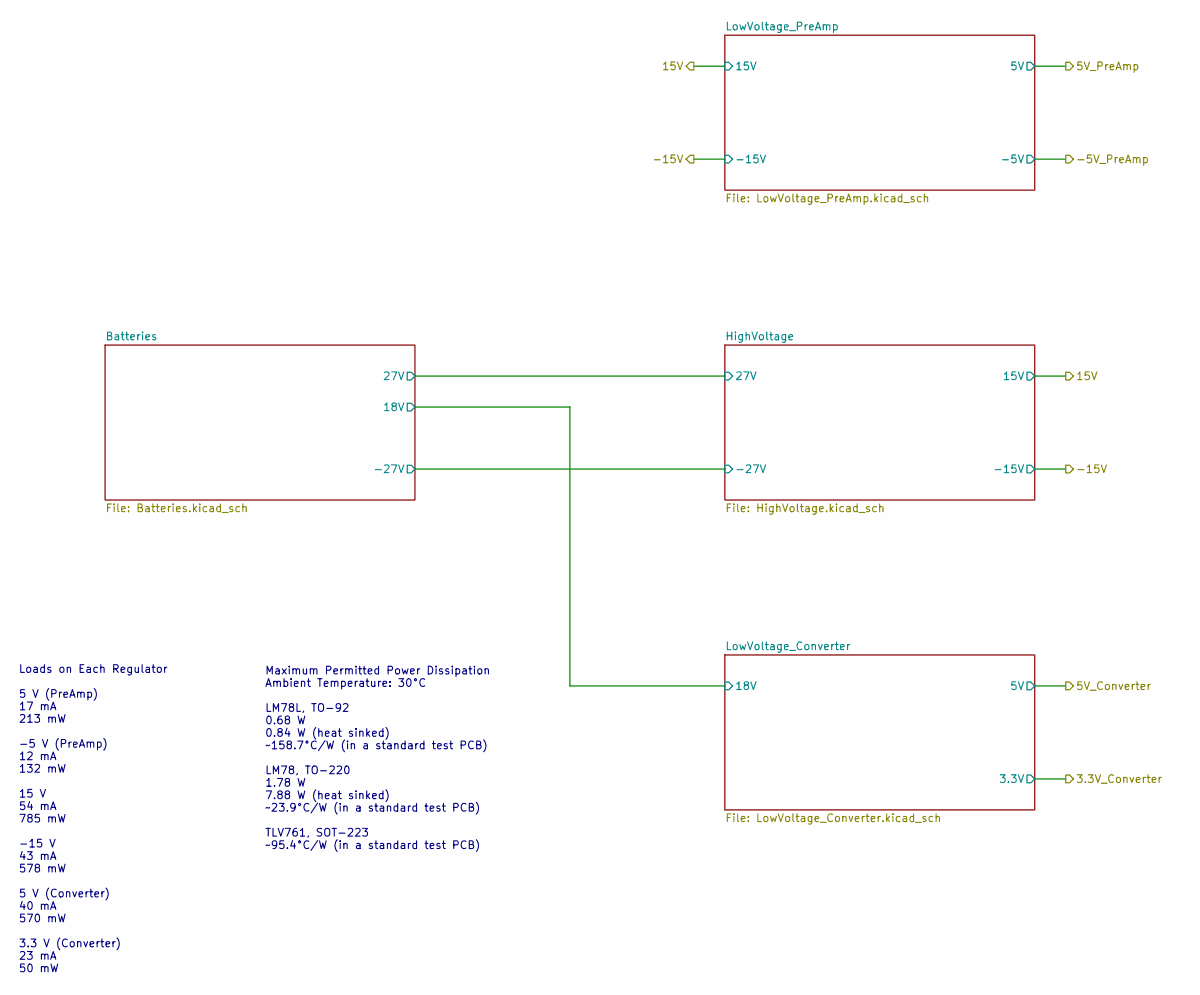
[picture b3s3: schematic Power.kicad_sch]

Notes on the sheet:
Loads on Each Regulator 5 V (PreAmp) 17 mA 213 mW -5 V (PreAmp) 12 mA 132 mW 15 V 54 mA 785 mW -15 V 43 mA 578 mW 5 V (Converter) 40 mA 570 mW 3.3 V (Converter) 23 mA 50 mW
Maximum Permitted Power Dissipation Ambient Temperature: 30°C LM78L, TO-92 0.68 W 0.84 W (heat sinked) ~158.7°C/W (in a standard test PCB) LM78, TO-220 1.78 W 7.88 W (heat sinked) ~23.9°C/W (in a standard test PCB) TLV761, SOT-223 ~95.4°C/W (in a standard test PCB)

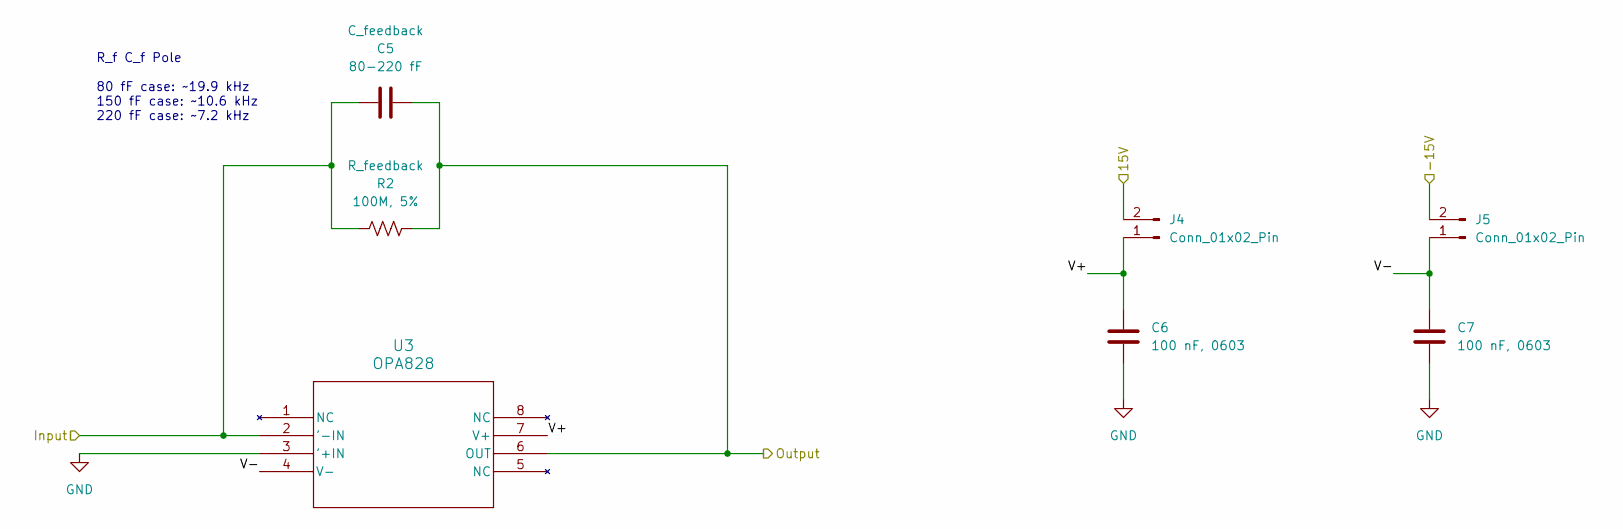
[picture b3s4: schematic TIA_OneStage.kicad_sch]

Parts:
C5: 80-220 fF
C6, C7: 100 nF, 0603; CAPC0603
J4, J5: Conn_01x02_Pin; PinHeader_1x2
R2: 100M, 5%; RESC0805
U3: OPA828; SOIC-8

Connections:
/15V: J4.2; also elsewhere on the board
/-15V: J5.2; also elsewhere on the board
/TIA_OneStage/Input: C5.1, R2.1, U3.2 ('-IN); also elsewhere on the board
/TIA_OneStage/Output: C5.2, R2.2, U3.6 (OUT); also elsewhere on the board
/TIA_OneStage/V+: C6.1, J4.1, U3.7 (V+)
/TIA_OneStage/V-: C7.1, J5.1, U3.4 (V-)
GND: C6.2, C7.2, U3.3 ('+IN); also elsewhere on the board

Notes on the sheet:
R_f C_f Pole 80 fF case: ~19.9 kHz 150 fF case: ~10.6 kHz 220 fF case: ~7.2 kHz

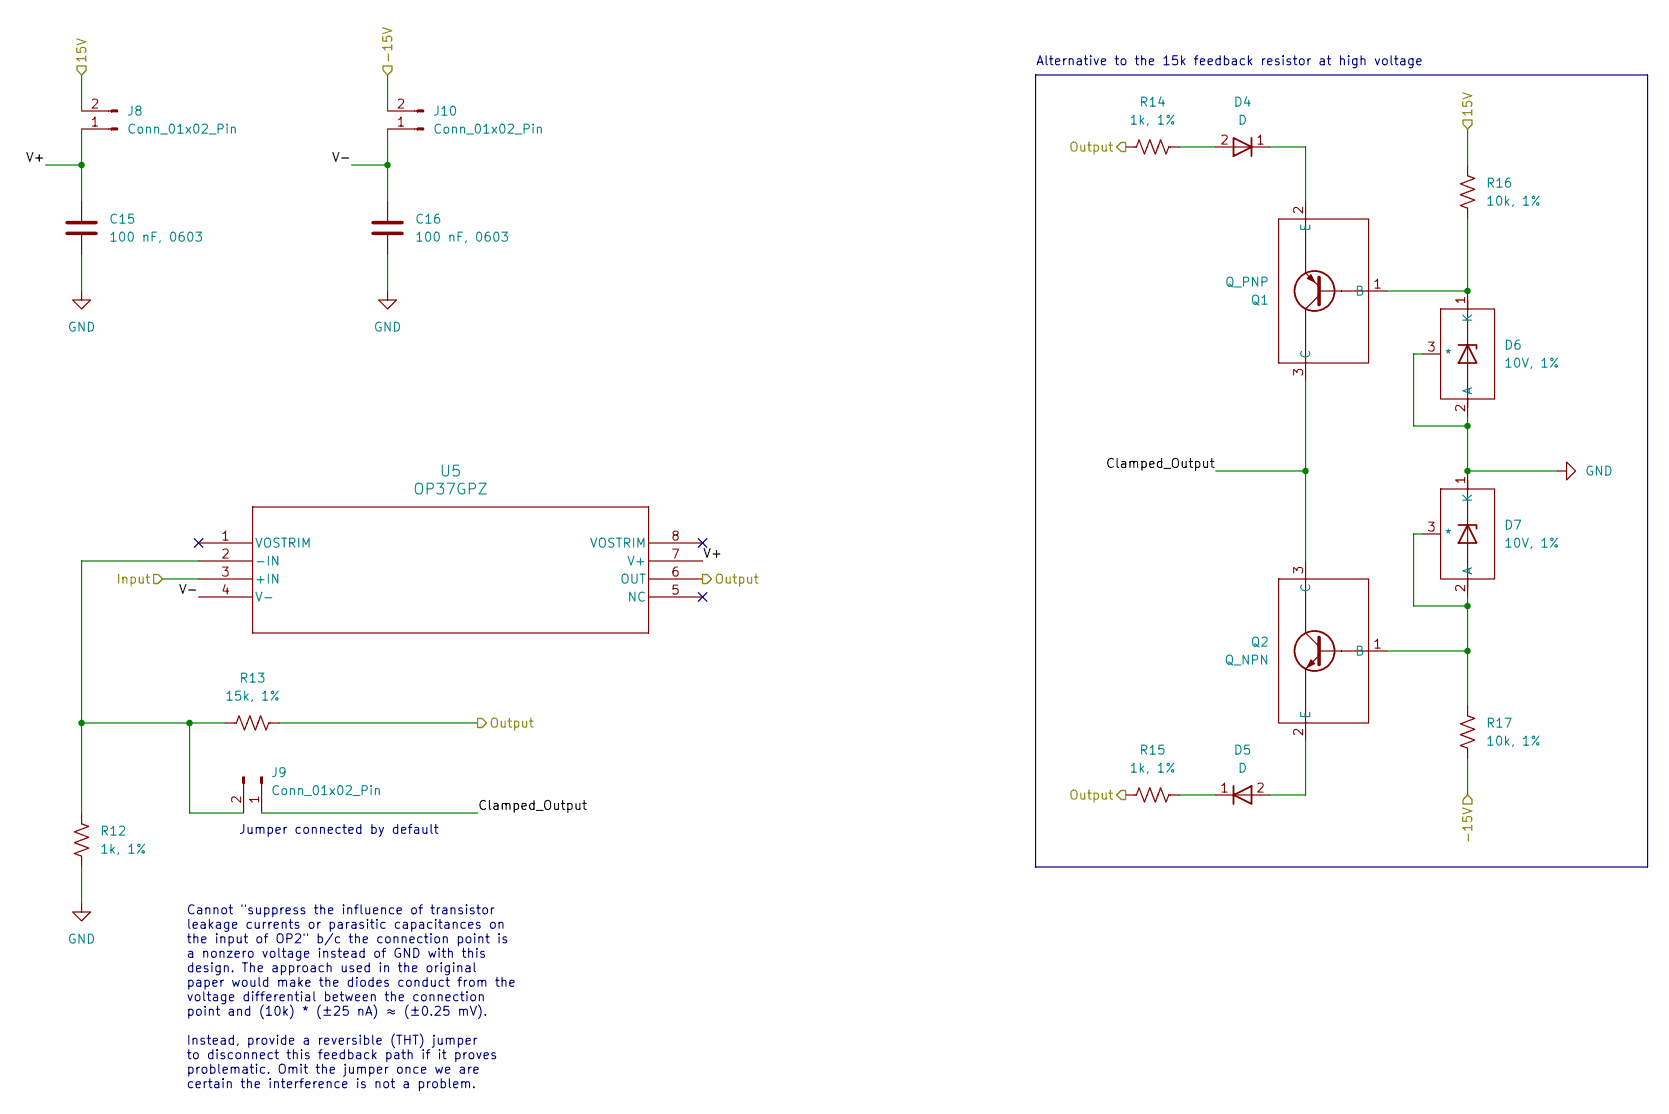
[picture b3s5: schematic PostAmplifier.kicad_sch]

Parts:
C15, C16: 100 nF, 0603; CAPC0603
D4, D5: D; SOD-123
D6, D7: 10V, 1%; SOT-23
J8, J9, J10: Conn_01x02_Pin; PinHeader_1x2
Q1: Q_PNP; SOT-23
Q2: Q_NPN; SOT-23
R12, R14, R15: 1k, 1%; RESC0603
R13: 15k, 1%; RESC0603
R16, R17: 10k, 1%; RESC0603
U5: OP37GPZ; PDIP-8

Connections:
/15V: J8.2, R16.1; also elsewhere on the board
/-15V: J10.2, R17.2; also elsewhere on the board
/TIA_TwoStage/Output: R13.2, R14.1, R15.1, U5.6 (OUT); also elsewhere on the board
/TIA_TwoStage/PostAmplifier/Clamped_Output: J9.1, Q1.3 (C), Q2.3 (C)
/TIA_TwoStage/PostAmplifier/Input: U5.3 (+IN); also elsewhere on the board
/TIA_TwoStage/PostAmplifier/V+: C15.1, J8.1, U5.7 (V+)
/TIA_TwoStage/PostAmplifier/V-: C16.1, J10.1, U5.4 (V-)
GND: C15.2, C16.2, D6.2 (A), D6.3 (*), D7.1 (K), R12.1; also elsewhere on the board
unnamed: D4.2 (A), R14.2
unnamed: D4.1 (K), Q1.2 (E)
unnamed: D5.2 (A), Q2.2 (E)
unnamed: D5.1 (K), R15.2
unnamed: D6.1 (K), Q1.1 (B), R16.2
unnamed: D7.2 (A), D7.3 (*), Q2.1 (B), R17.1
unnamed: J9.2, R12.2, R13.1, U5.2 (-IN)

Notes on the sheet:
Cannot "suppress the influence of transistor leakage currents or parasitic capacitances on the input of OP2" b/c the connection point is a nonzero voltage instead of GND with this design. The approach used in the original paper would make the diodes conduct from the voltage differential between the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
Jumper connected by default
Alternative to the 15k feedback resistor at high voltage

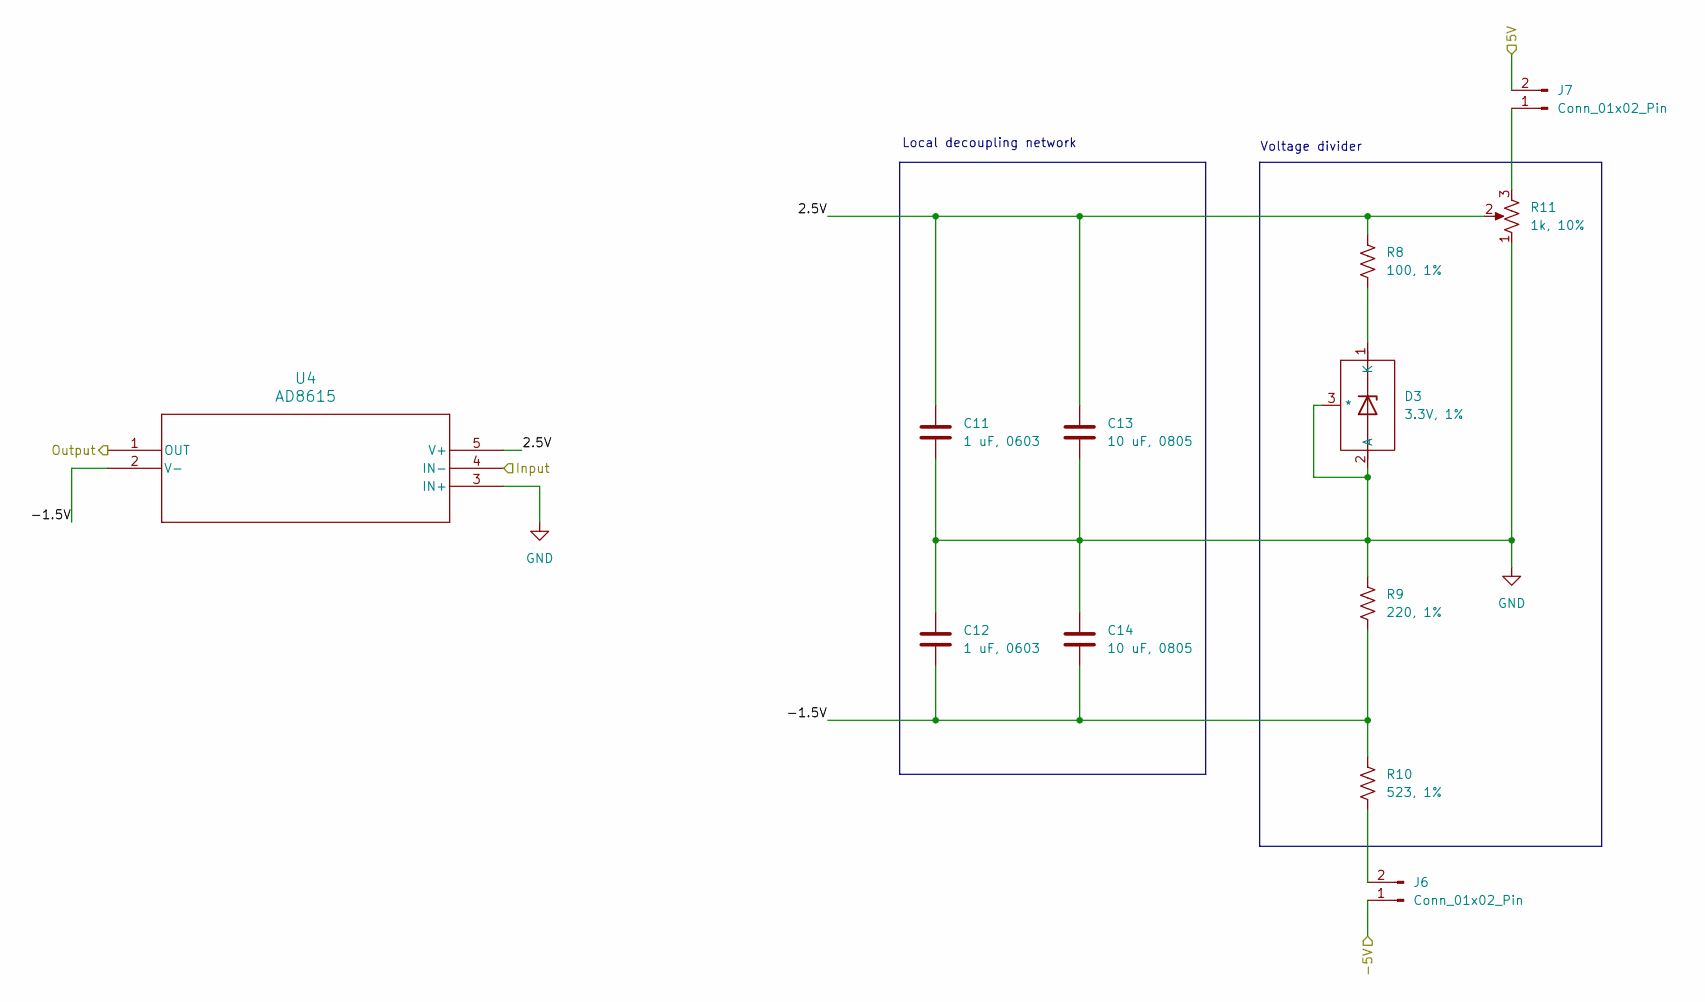
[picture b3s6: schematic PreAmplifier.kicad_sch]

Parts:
C11, C12: 1 uF, 0603; CAPC0603
C13, C14: 10 uF, 0805; CAPC0805
D3: 3.3V, 1%; SOT-23
J6, J7: Conn_01x02_Pin; PinHeader_1x2
R8: 100, 1%; RESC0603
R9: 220, 1%; RESC0603
R10: 523, 1%; RESC0603
R11: 1k, 10%; Bourns_3296Y
U4: AD8615

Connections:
/5V_PreAmp: J7.2; also elsewhere on the board
/-5V_PreAmp: J6.1; also elsewhere on the board
/TIA_TwoStage/Input: U4.4 (IN-); also elsewhere on the board
/TIA_TwoStage/PostAmplifier/Input: U4.1 (OUT); also elsewhere on the board
/TIA_TwoStage/PreAmplifier/2.5V: C11.1, C13.1, R8.1, R11.2, U4.5 (V+)
/TIA_TwoStage/PreAmplifier/-1.5V: C12.2, C14.2, R9.2, R10.1, U4.2 (V-)
GND: C11.2, C12.1, C13.2, C14.1, D3.2 (A), D3.3 (*), R9.1, R11.1, U4.3 (IN+); also elsewhere on the board
unnamed: D3.1 (K), R8.2
unnamed: J6.2, R10.2
unnamed: J7.1, R11.3

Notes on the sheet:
Voltage divider
Local decoupling network
